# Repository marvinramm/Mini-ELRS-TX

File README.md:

# Mini 2.4 GHz TX for ExpressLRS

**A compact open-hardware transmitter module for the [ExpressLRS](https://github.com/ExpressLRS/ExpressLRS) radio link. It is a 2-layer board of only 19.75 × 29.25 mm with an ESP32, an SX1280 radio module and a U.FL connector for Wi-Fi.**

ExpressLRS is an open-source radio link between RC transmitter and model with low latency and long range. I designed this board in 2022 as my own small alternative to the commercial TX modules. It runs the unmodified ExpressLRS firmware.

## Hardware

| | |
|---|---|
| **MCU** | ESP32-D0WDQ6 with 4 MB SPI flash (W25Q32), 40 MHz crystal |
| **Radio** | Ebyte E28-2G4M12S (Semtech SX1280, 2.4 GHz, 12.5 dBm ≈ 18 mW, no external PA), on the bottom side |
| **Antennas** | PCB antenna of the E28 module for the RC link; U.FL connector for the Wi-Fi/Bluetooth antenna of the ESP32 (updates and configuration over Wi-Fi) |
| **Power** | `VCC` via AMS1117-3.3. Solder jumper `JP2` bypasses the regulator if the module is supplied with 3.3 V directly. |
| **Interface** | Single-wire serial (`SPORT`) to the radio, the standard interface of ExpressLRS TX modules |
| **PCB** | 2 layers, 19.75 × 29.25 mm, 1.2 mm thick, minimum trace width 0.15 mm |

### Pads

The eight pads at the top edge carry everything that is needed for flashing and operation. The assignment is also printed on the bottom silkscreen.

| Pad | Signal | Pad | Signal |
|---|---|---|---|
| 1 | `BOOT` (GPIO0) | 2 | `TX` (U0TXD) |
| 3 | `RST` (EN) | 4 | `RX` (U0RXD) |
| 5 | `GND` | 6 | `3V3` |
| 7 | `VCC` (regulator input) | 8 | `SPORT` (GPIO13) |

### ESP32 ↔ SX1280

| Signal | GPIO | Signal | GPIO |
|---|---|---|---|
| `NSS` | 5 | `BUSY` | 21 |
| `SCK` | 18 | `DIO1` | 4 |
| `MOSI` | 23 | `DIO2` | 2 |
| `MISO` | 19 | `NRESET` | 14 |

## Firmware

The firmware is the official **ExpressLRS** firmware ([ExpressLRS/ExpressLRS](https://github.com/ExpressLRS/ExpressLRS), GPL-3.0). It is not part of this repository. Build and flash it with the [ExpressLRS Configurator](https://github.com/ExpressLRS/ExpressLRS-Configurator) for a generic ESP32 2.4 GHz TX with the pin assignment above.

For the first upload, connect a 3.3 V USB-to-UART adapter to `TX`, `RX`, `GND` and `3V3`, and pull `BOOT` to `GND` during reset. After that, updates work over Wi-Fi.

## Build

The Gerber, drill and pick-and-place files are attached to the [release](https://github.com/marvinramm/ExpressLRS/releases). The parts are listed in the [BOM](hardware/mini-tx-rev1/Mini-ELRS-TX-REV1_BOM.csv). Order the PCB with 1.2 mm thickness.

```
hardware/mini-tx-rev1/    Schematic (PDF), BOM, EAGLE schematic and board in source/
docs/images/              Pictures used in this README
```

### Open point

- [ ] Add a separate `BOOT`-to-`GND` pad or button, so the first upload works without wiring a jumper

## License

© 2022 Marvin Ramm. The hardware design files, images and documentation are licensed under [CC BY 4.0](LICENSE): commercial use is allowed if you credit "Mini 2.4 GHz TX by Marvin Ramm" with a link to this repository. Details are in [LICENSING.md](LICENSING.md).

The ExpressLRS firmware is a separate project under GPL-3.0. "ExpressLRS" is a trademark of ExpressLRS LLC. This board is a community design and not an official ExpressLRS product.

> The use of radio transmitters may require a license, and some countries restrict it. You are responsible for complying with your local regulations.

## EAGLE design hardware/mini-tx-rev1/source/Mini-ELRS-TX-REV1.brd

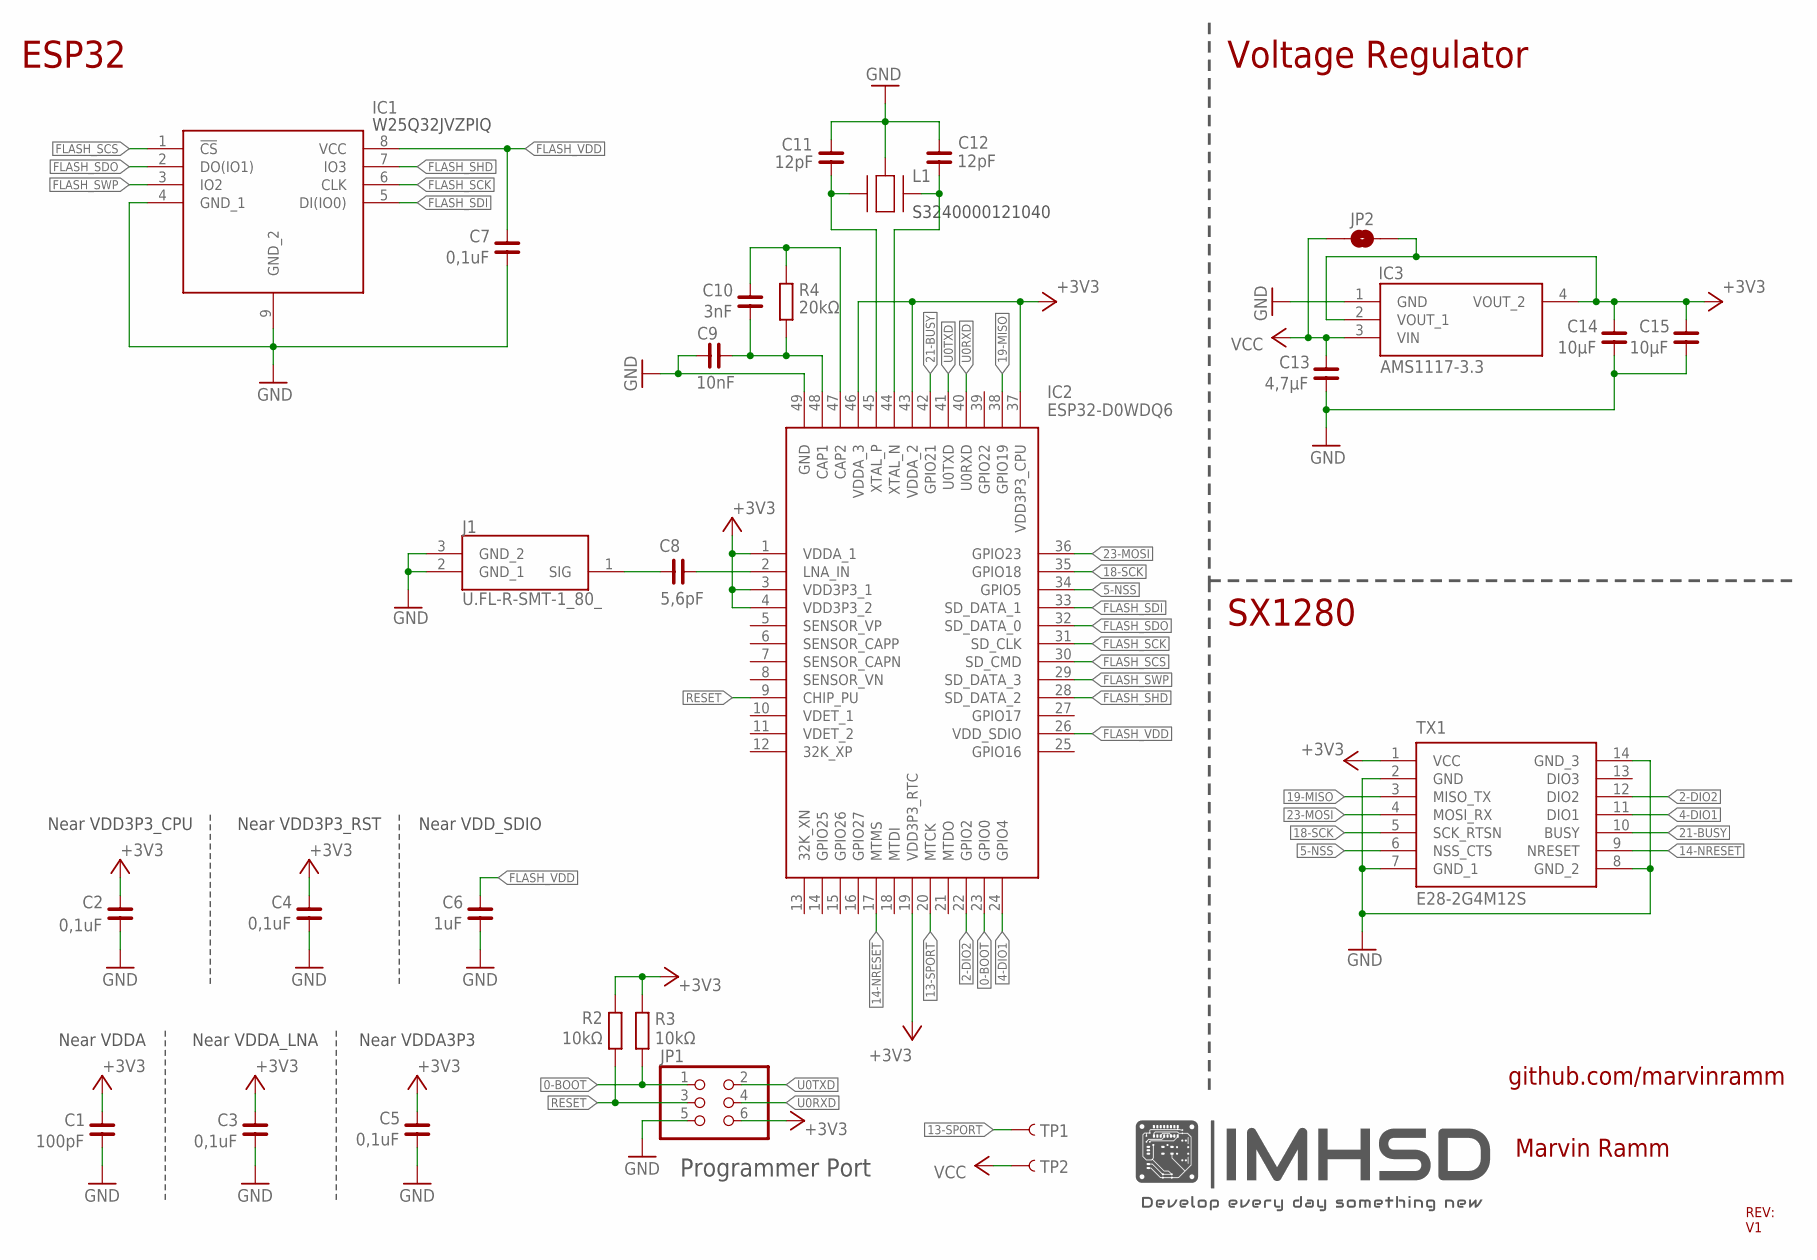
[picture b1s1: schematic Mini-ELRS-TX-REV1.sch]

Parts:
C1: 100pF; C0402
C2, C3, C4, C5, C7: 0,1uF; C0402
C6: 1uF; C0402
C8: 5,6pF; C0402
C9: 10nF; C0402
C10: 3nF; C0402
C11, C12: 12pF; C0402
C13: 4,7µF; C0603
C14, C15: 10µF; C0603
IC1: W25Q128JVPIQ; SON127P800X600X80-9N
IC2: ESP32-D0WDQ6; QFN40P600X600X90-49N
IC3: AMS1117-3.3; SOT229P700X180-4N
J1: U.FL-R-SMT-1_80_; UFLRSMT180
JP1: ESP32_PRG_PORT
JP2: JUMPER-SMT_2_NO_SILK; SMT-JUMPER_2_NO_SILK
L1: SMD-3225_4P16MHZ_20PF_10PPM_-4; SMD3225_4P16MHZ20PF10PPM4085
R2, R3: 10kΩ; R0402
R4: 20kΩ; R0402
TP1, TP2: TEST-POINT3X5; PAD.03X.05
TX1: E28-2G4M12S

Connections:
0-BOOT: IC2.23 (GPIO0), JP1.1, R3.2
2-DIO2: IC2.22 (GPIO2), TX1.12 (DIO2)
4-DIO1: IC2.24 (GPIO4), TX1.11 (DIO1)
5-NSS: IC2.34 (GPIO5), TX1.6 (NSS_CTS)
13-SPORT: IC2.20 (MTCK), TP1.1
14-NRESET: IC2.17 (MTMS), TX1.9 (NRESET)
18-SCK: IC2.35 (GPIO18), TX1.5 (SCK_RTSN)
19-MISO: IC2.38 (GPIO19), TX1.3 (MISO_TX)
21-BUSY: IC2.42 (GPIO21), TX1.10 (BUSY)
23-MOSI: IC2.36 (GPIO23), TX1.4 (MOSI_RX)
+3V3: C1.2, C2.2, C3.2, C4.2, C5.2, C14.1, C15.1, IC2.1 (VDDA_1), IC2.3 (VDD3P3_1), IC2.4 (VDD3P3_2), IC2.19 (VDD3P3_RTC), IC2.37 (VDD3P3_CPU), IC2.43 (VDDA_2), IC2.46 (VDDA_3), IC3.2 (VOUT_1), IC3.4 (VOUT_2), JP1.6, JP2.2, R2.2, R3.1, TX1.1 (VCC)
FLASH_SCK: IC1.6 (CLK), IC2.31 (SD_CLK)
FLASH_SCS: IC1.1 (!CS), IC2.30 (SD_CMD)
FLASH_SDI: IC1.5 (DI(IO0)), IC2.33 (SD_DATA_1)
FLASH_SDO: IC1.2 (DO(IO1)), IC2.32 (SD_DATA_0)
FLASH_SHD: IC1.7 (IO3), IC2.28 (SD_DATA_2)
FLASH_SWP: IC1.3 (IO2), IC2.29 (SD_DATA_3)
FLASH_VDD: C6.2, C7.2, IC1.8 (VCC), IC2.26 (VDD_SDIO)
GND: C1.1, C2.1, C3.1, C4.1, C5.1, C6.1, C7.1, C9.1, C11.1, C12.1, C13.2, C14.2, C15.2, IC1.4 (GND_1), IC1.9 (GND_2), IC2.49 (GND), IC3.1 (GND), J1.2 (GND_1), J1.3 (GND_2), JP1.5, L1.2 (GND_2), L1.4 (GND_2), TX1.2 (GND), TX1.7 (GND_1), TX1.8 (GND_2), TX1.14 (GND_3)
unnamed: C8.2, J1.1 (SIG)
unnamed: C8.1, IC2.2 (LNA_IN)
unnamed: C9.2, C10.1, IC2.48 (CAP1), R4.2
unnamed: C10.2, IC2.47 (CAP2), R4.1
unnamed: C12.2, IC2.44 (XTAL_N), L1.3 (CRYSTAL_2)
unnamed: C11.2, IC2.45 (XTAL_P), L1.1 (CRYSTAL_1)
RESET: IC2.9 (CHIP_PU), JP1.3, R2.1
U0RXD: IC2.40 (U0RXD), JP1.4
U0TXD: IC2.41 (U0TXD), JP1.2
VCC: C13.1, IC3.3 (VIN), JP2.1, TP2.1

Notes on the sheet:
S3240000121040
Near VDDA
Near VDDA_LNA
Near VDDA3P3
Near VDD3P3_CPU
Near VDD3P3_RST
Near VDD_SDIO
Programmer Port
W25Q32JVZPIQ
Marvin Ramm
REV: V1
github.com/marvinramm
ESP32
Voltage Regulator
SX1280

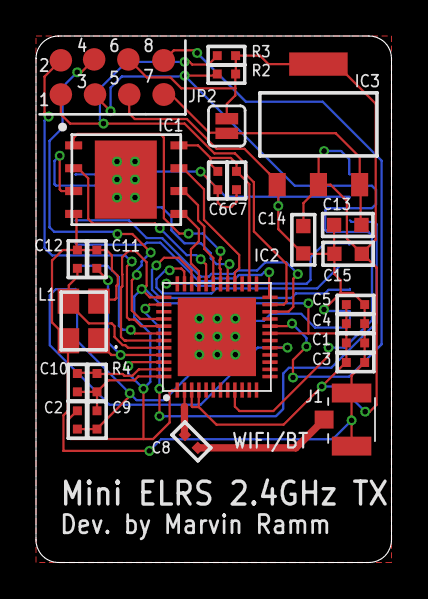
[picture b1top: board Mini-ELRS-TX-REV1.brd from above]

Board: 2 copper layers, 19.8 x 29.2 mm, 28 parts (1 on the bottom side), 29 nets.

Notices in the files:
README.md:
License: CC BY 4.0
parts and their libraries:
rc-master-smd: Copyright (C) 2007, Bob Starr
SparkFun-Jumpers: Licensing: Creative Commons ShareAlike 4.0 International - https://creativecommons.org/licenses/by-sa/4.0
